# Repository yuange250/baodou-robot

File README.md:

# Brufik in One

Monorepo combining **Brufik hardware/firmware** and **opendesk-service backend**.

> The current Baodou robot runs the ESP32-to-Doubao Realtime direct firmware. See the Chinese [`firmware development and flashing guide`](docs/firmware-development-and-flashing.md) for the source map, local setup, Windows flashing, logs, smoke tests, and Coding Agent handoff notes.

| Directory | Description |
|-----------|-------------|
| [`hardware/`](hardware/) | ESP32S3 firmware, mechanical assets, PCB rebuild files, flash scripts |
| [`service/`](service/) | Voice backend: VAD → ASR → LLM → TTS, WebSocket `/asr_chat`, web console |

## Quick start

### 1. Backend (service)

```bash
cd service
cp .env.example .env
# Edit .env — set LLM_API_KEY
chmod +x start.sh
./start.sh
```

Web console: `http://<host>:5050/` · Device WS: `ws://<host>:9000/asr_chat`

See [`service/README.md`](service/README.md).

### 2. Firmware (hardware)

```bash
cd hardware
# Copy firmware/deskbot_local_config.example.h to the ignored
# firmware/deskbot_local_config.h, then fill in local values.
./flash_rom.sh all
```

See [`hardware/README.md`](hardware/README.md) and [`hardware/README_zh.md`](hardware/README_zh.md).

For direct Realtime firmware, local credentials, Windows flashing, and safe GitHub publishing, see
[`docs/local-config-and-github.md`](docs/local-config-and-github.md).

For the current firmware architecture and complete edit/build/flash workflow, see
[`docs/firmware-development-and-flashing.md`](docs/firmware-development-and-flashing.md).

## License

- **Hardware** ([`hardware/mechanical/`](hardware/mechanical/)): CERN-OHL-S-2.0
- **Firmware** ([`hardware/firmware/`](hardware/firmware/)): GPL-3.0
- **Service** ([`service/`](service/)): GPL-3.0

See respective `LICENSE` files in each subtree.

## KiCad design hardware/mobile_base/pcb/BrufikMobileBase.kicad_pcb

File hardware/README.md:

# Brufik

[中文](README_zh.md) | English

**Hardware in this repository is under [CERN-OHL-S-2.0](mechanical/LICENSE); software is under [GPL-3.0](firmware/LICENSE).**

**Brufik** is an open-source deskbot on **Seeed XIAO ESP32S3 Sense**. Backend: [open-deskbot-service](https://github.com/OpenDeskBot/open-deskbot-service).

---

## 1. Out of the box

1. Copy [`firmware/deskbot_local_config.example.h`](firmware/deskbot_local_config.example.h) to the ignored `firmware/deskbot_local_config.h`, then set the local Wi-Fi values.
2. Power on — the device joins that WiFi and talks to your backend.
3. To use another SSID: power on the deskbot, join AP **`Deskbot_Rom`**, then open the address shown on the screen, usually **`http://192.168.4.1/`**. The onboarding page lets you pick or type your home WiFi and save it. For compile-time defaults, edit only the ignored `deskbot_local_config.h`.

---

## 2. Developers

The current Baodou unit uses the ESP32-to-Doubao Realtime direct firmware. On Windows, use `scripts/build_direct.ps1` so the ignored local Realtime/Ark credentials are injected at build time. See the Chinese [`firmware development and flashing guide`](../docs/firmware-development-and-flashing.md) for the complete workflow.

Create the ignored `firmware/deskbot_local_config.h` from its example, then:

```bash
./flash_rom.sh all
```

Deploy [open-deskbot-service](https://github.com/OpenDeskBot/open-deskbot-service). Firmware WebSocket: **`/asr_chat`**.

Optional debug: `http://<device-ip>/` for a local camera page.

---

## 3. DIY assembly

| Part | Notes | Search terms |
|------|-------|----------------|
| MCU | Camera module + **onboard mic** on the Sense board (**no extra purchase**) | Seeed XIAO ESP32S3 **Sense** |
| Lens | For **OV2640**; **120°** wide angle; **same-plane** (not off-axis); **25 mm** length | `OV2640 lens 120° same plane 25mm` |
| LCD | 1.83" SPI ST7789 240×284 | Waveshare 1.83 LCD Rev2 |
| Servos | **Large + small**; pan = **2g micro servo**, tilt = larger servo | `2g servo`, `SG90` / `9g servo` |
| Amp | I2S | MAX98357A |
| Speaker | **2011** type | `2011 speaker`, `8Ω 2011` |
| Power | 5V ≥1A for servos | — |
| PCB | This repo includes an extension **PCB** for easier wiring; **hand-wiring without the PCB also works** | — |

### Assembly guide & reference photos

- **Step-by-step manual:** [`mechanical/说明书1.02PDF.pdf`](mechanical/说明书1.02PDF.pdf)
- **All parts laid out:** [`mechanical/parts-overview.png`](mechanical/parts-overview.png)
- **Core assembly done (shell not installed):** [`mechanical/assembly-without-shell.png`](mechanical/assembly-without-shell.png)
- **Side view without shell:** [`mechanical/assembly-side-no-shell.png`](mechanical/assembly-side-no-shell.png)

### Wiring (XIAO pad → device)

> Schematic **IO8 / IO3** = **GPIO numbers**, not silkscreen D8/D3.

| Device | Signals | XIAO pads |
|--------|---------|-----------|
| LCD SPI | MOSI/CLK/CS/DC | D10 / D8 / D1 / D2 |
| Servo X (pan) | PWM | **D9 / GPIO8** (2g; firmware applies 2:1 gain and tool-layer mirroring) |
| Servo Y (tilt) | PWM | **D3 / GPIO4** (large; lower logical values tilt upward) |
| MAX98357 | DIN/BCLK/LRC | D0 / D5 / D4 → 2011 speaker |
| Mic | PDM | **Onboard** (ESP32S3 Sense) |

Details: [`firmware/deskbot_config.h`](firmware/deskbot_config.h).

---

## License

| Scope | License | File |
|-------|---------|------|
| Hardware ([`mechanical/`](mechanical/)) | CERN-OHL-S-2.0 | [`mechanical/LICENSE`](mechanical/LICENSE) |
| Software ([`firmware/`](firmware/) etc.) | GNU GPL v3.0 | [`firmware/LICENSE`](firmware/LICENSE) |

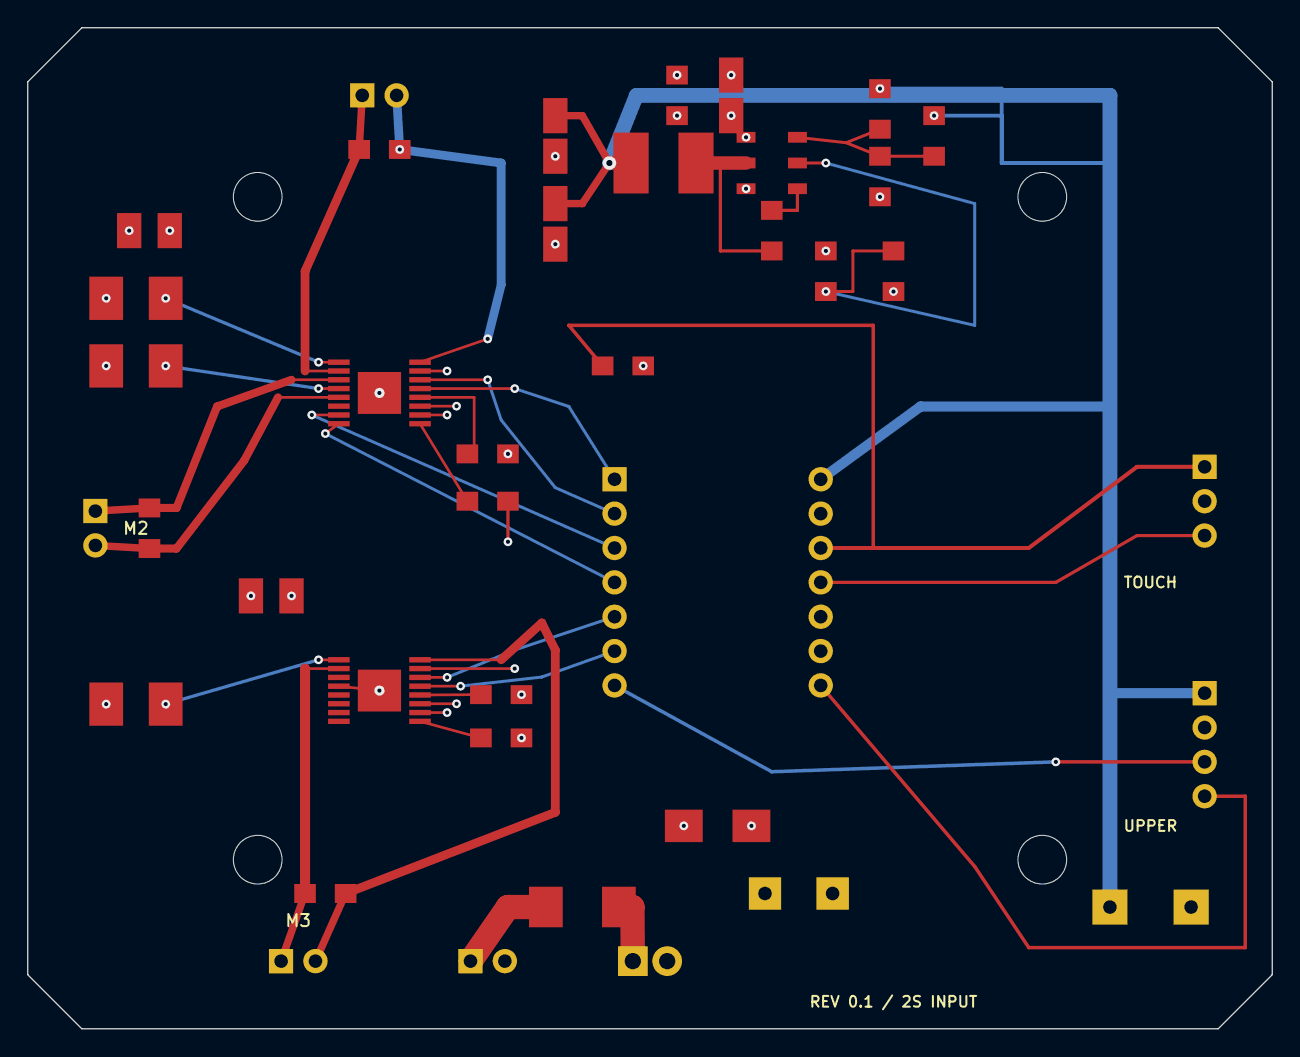
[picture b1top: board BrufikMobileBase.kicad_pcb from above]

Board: 4 copper layers, 92.0 x 74.0 mm, 43 parts (0 on the bottom side), 33 nets.

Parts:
C1, C3, C4: 22uF
C2, C5, C15, C16, C17: 100nF
C6: 75pF
C7: 470uF
C8: 1000uF
C9, C12: 10uF
C10, C13: 2.2uF
C11, C14: 10nF
D1: SMBJ10A
F1: 5A PTC
H1, H2, H3, H4: M3
J1: BATTERY 2S
J2: POWER SWITCH
J3: MOTOR 1
J4: MOTOR 2
J5: MOTOR 3
J6: UPPER LINK
J7: TOUCH
L1: 10uH
R1, R3: 100k
R2: 13.3k
R4: 47k
R5: 10k
R7, R8, R9: 0.20R
U1: TPS54302DDCR
U2, U3: DRV8833PWPR
U4: Seeed XIAO ESP32-C3

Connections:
+3V3: J7.1, R5.1, U4.R3
+5V: C3.1, C4.1, C6.1, C8.1, J6.1, L1.1, R1.1, U4.R1
BAT_FUSED: F1.1, J2.1
BAT_RAW: F1.2, J1.1
BUCK_BOOT: C5.1, U1.6
BUCK_EN: R3.2, R4.1, U1.5
BUCK_FB: C6.2, R1.2, R2.1, U1.4
BUCK_SW: C5.2, L1.2, U1.2
GND: C1.1, C2.1, C3.2, C4.2, C7.2, C8.2, C9.2, C10.2, C12.2, C13.2, D1.2, J1.2, J6.2, J7.2, R2.2, R4.2, R7.1, R8.1, R9.1, U1.1, U2.11, U2.17, U3.4, U3.11, U3.17, U4.R2
M1_A: C15.2, J3.2, U2.16
M1_B: C15.1, J3.1, U2.2
M1_IN1: U2.14, U4.L2
M1_IN2: U2.13, U4.L1
M2_A: C16.2, J4.2, U2.5
M2_B: C16.1, J4.1, U2.3
M2_IN1: U2.7, U4.L3
M2_IN2: U2.8, U4.L4
M3_A: C17.2, J5.2, U3.16
M3_B: C17.1, J5.1, U3.2
M3_IN1: U3.14, U4.L5
M3_IN2: U3.13, U4.L6
SLEEP: R5.2, U2.15, U3.15
TOUCH: J7.3, U4.R4
U2_SENSE_A: R7.2, U2.1
U2_SENSE_B: R8.2, U2.4
U2_VCP: C11.1, U2.9
U2_VINT: C10.1, U2.12
U3_SENSE_A: R9.2, U3.1
U3_VCP: C14.1, U3.9
U3_VINT: C13.1, U3.12
UART_RX: J6.4, U4.R7
UART_TX: J6.3, U4.L7
VBAT: C1.2, C2.2, C7.1, C9.1, C11.2, C12.1, C14.2, D1.1, J2.2, R3.1, U1.3, U2.10, U3.10

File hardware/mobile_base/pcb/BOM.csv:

Reference,Value,Footprint,Description,LCSC,Assembly
U1,TPS54302DDCR,SOT-23-6,5V/3A synchronous buck,C129704,SMT
U2,DRV8833PWPR,HTSSOP-16-EP,Dual H-bridge for M1/M2,,SMT
U3,DRV8833PWPR,HTSSOP-16-EP,Dual H-bridge for M3,,SMT
U4,Seeed XIAO ESP32-C3,XIAO-2x7-P2.54,Base motion MCU,,HAND
F1,5A resettable fuse,PTC-2920,Battery branch protection,,SMT
D1,SMBJ10A,SMB,Battery transient suppressor,C83357,SMT
L1,10uH 4A shielded,IND-7x7,5V buck output inductor,,SMT
C1,22uF 16V X7R,C1210,Buck input capacitor,,SMT
C2,100nF 25V X7R,C0805,Buck HF input bypass,,SMT
C3,22uF 10V X7R,C1210,5V output capacitor,,SMT
C4,22uF 10V X7R,C1210,5V output capacitor,,SMT
C5,100nF 16V X7R,C0805,TPS54302 bootstrap capacitor,,SMT
C6,75pF C0G,C0805,5V feedback feed-forward capacitor,,SMT
C7,470uF 16V low-ESR,CP-RADIAL-D8,Motor/battery local bulk,,HAND
C8,1000uF 10V low-ESR,CP-RADIAL-D10,Upper-body 5V surge bulk,,HAND
C9,10uF 16V X7R,C1210,U2 VM local bypass,,SMT
C10,2.2uF 10V X7R,C0805,U2 VINT bypass,,SMT
C11,10nF 16V X7R,C0805,U2 VCP capacitor,,SMT
C12,10uF 16V X7R,C1210,U3 VM local bypass,,SMT
C13,2.2uF 10V X7R,C0805,U3 VINT bypass,,SMT
C14,10nF 16V X7R,C0805,U3 VCP capacitor,,SMT
C15,100nF 25V X7R,C0805,M1 EMI capacitor,,SMT
C16,100nF 25V X7R,C0805,M2 EMI capacitor,,SMT
C17,100nF 25V X7R,C0805,M3 EMI capacitor,,SMT
R1,100k 1%,R0805,5V feedback upper resistor,,SMT
R2,13.3k 1%,R0805,5V feedback lower resistor,,SMT
R3,100k 1%,R0805,Buck enable upper resistor,,SMT
R4,47k 1%,R0805,Buck enable lower resistor,,SMT
R5,10k,R0805,DRV nSLEEP pull-up,,SMT
R7,0.20R 1W 1%,R2512,"M1 current limit, about 1A",,SMT
R8,0.20R 1W 1%,R2512,"M2 current limit, about 1A",,SMT
R9,0.20R 1W 1%,R2512,"M3 current limit, about 1A",,SMT
J1,BATTERY 2S,TERM-2P-P5.08,Protected 2S battery input,,HAND
J2,POWER SWITCH,JST-XH-2P,External latching switch or jumper,,HAND
J3,MOTOR 1,JST-XH-2P,N20 motor 1,,HAND
J4,MOTOR 2,JST-XH-2P,N20 motor 2,,HAND
J5,MOTOR 3,JST-XH-2P,N20 motor 3,,HAND
J6,UPPER LINK,JST-XH-4P,5V/GND/TX/RX to current robot,,HAND
J7,TOUCH,JST-XH-3P,3.3V/GND/touch signal,,HAND

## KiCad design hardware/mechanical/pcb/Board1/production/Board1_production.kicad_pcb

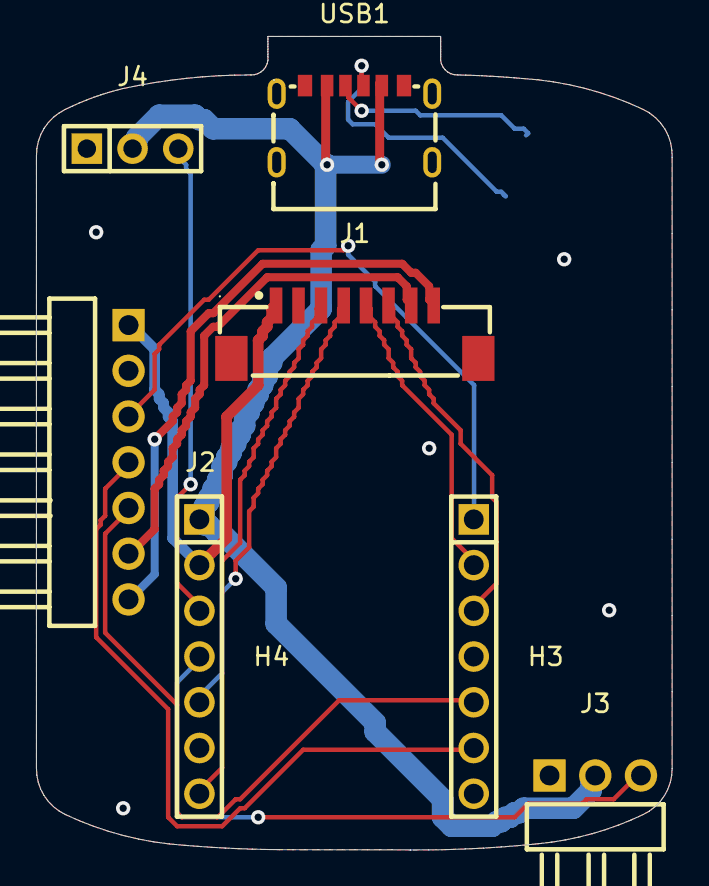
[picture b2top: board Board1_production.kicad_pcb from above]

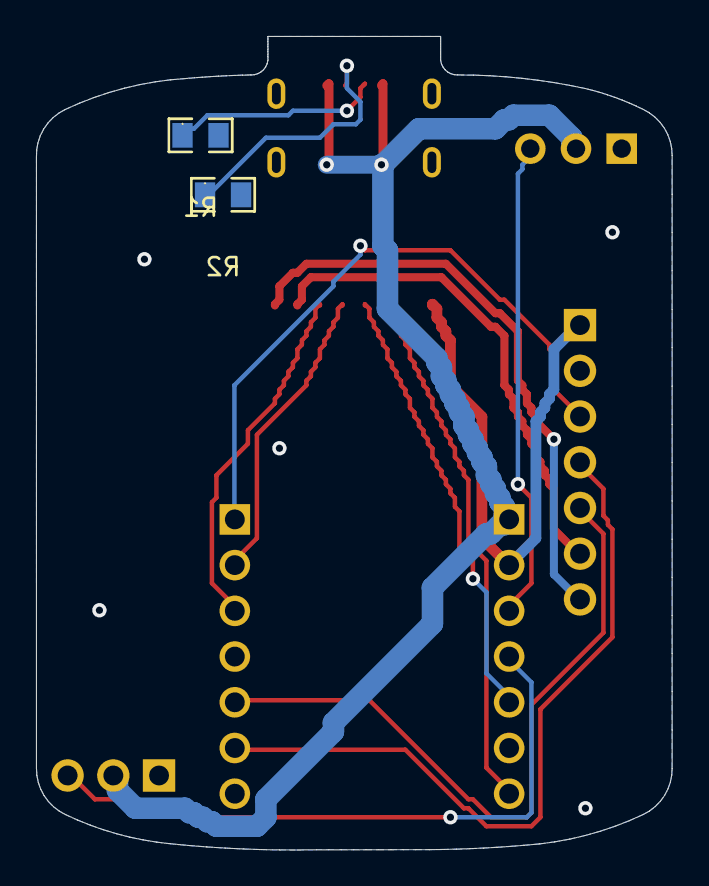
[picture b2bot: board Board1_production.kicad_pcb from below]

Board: 2 copper layers, 35.3 x 45.2 mm, 9 parts (2 on the bottom side), 16 nets.

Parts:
H3: XIAO_A; HDR-TH_7P-P2.54-V-M
H4: XIAO_B; HDR-TH_7P-P2.54-V-M
J1: HEAD_8P; CONN-SMD_8P-P1.25_ZX-MX1.25-8PLT
J2: AMP_7P; HDR-TH_7P-P2.54-H-M-W10.4
J3: SERVO_X; HDR-TH_3P-P2.54-H-M-W10.4
J4: SERVO_Y; HDR-TH_3P-P2.54-V-M_PZ254V-11-03P
R1: 5.1k CC1; R0805
R2: 5.1k CC2; R0805
USB1: TYPE-C 6P(073); TYPE-C-SMD_TYPE-C-6P-073

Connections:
+3V3: H4.2, J1.1, J2.1
+5V: H4.1, J3.2, J4.2, USB1.A9, USB1.B9
CC1: R1.1, USB1.A5
CC2: R2.1, USB1.B5
D0/I2S_DIN: H3.1, J2.3
D1/LCD_CS: H3.2, J1.5
D2/LCD_DC: H3.3, J1.6
D4/I2S_LRC: H3.5, J2.5
D5/I2S_BCLK: H3.6, J2.4
D6/SERVO_Y: H4.3, J4.3
D7/SERVO_X: H4.4, J3.3
D8/LCD_SCK: H4.5, J1.4
D10/LCD_MOSI: H4.7, J1.3
GND: H3.7, J1.2, J1.9, J1.10, J2.2, J3.1, J4.1, R1.2, R2.2, USB1.7, USB1.A12, USB1.B12
SPK+: J1.7, J2.6
SPK-: J1.8, J2.7
